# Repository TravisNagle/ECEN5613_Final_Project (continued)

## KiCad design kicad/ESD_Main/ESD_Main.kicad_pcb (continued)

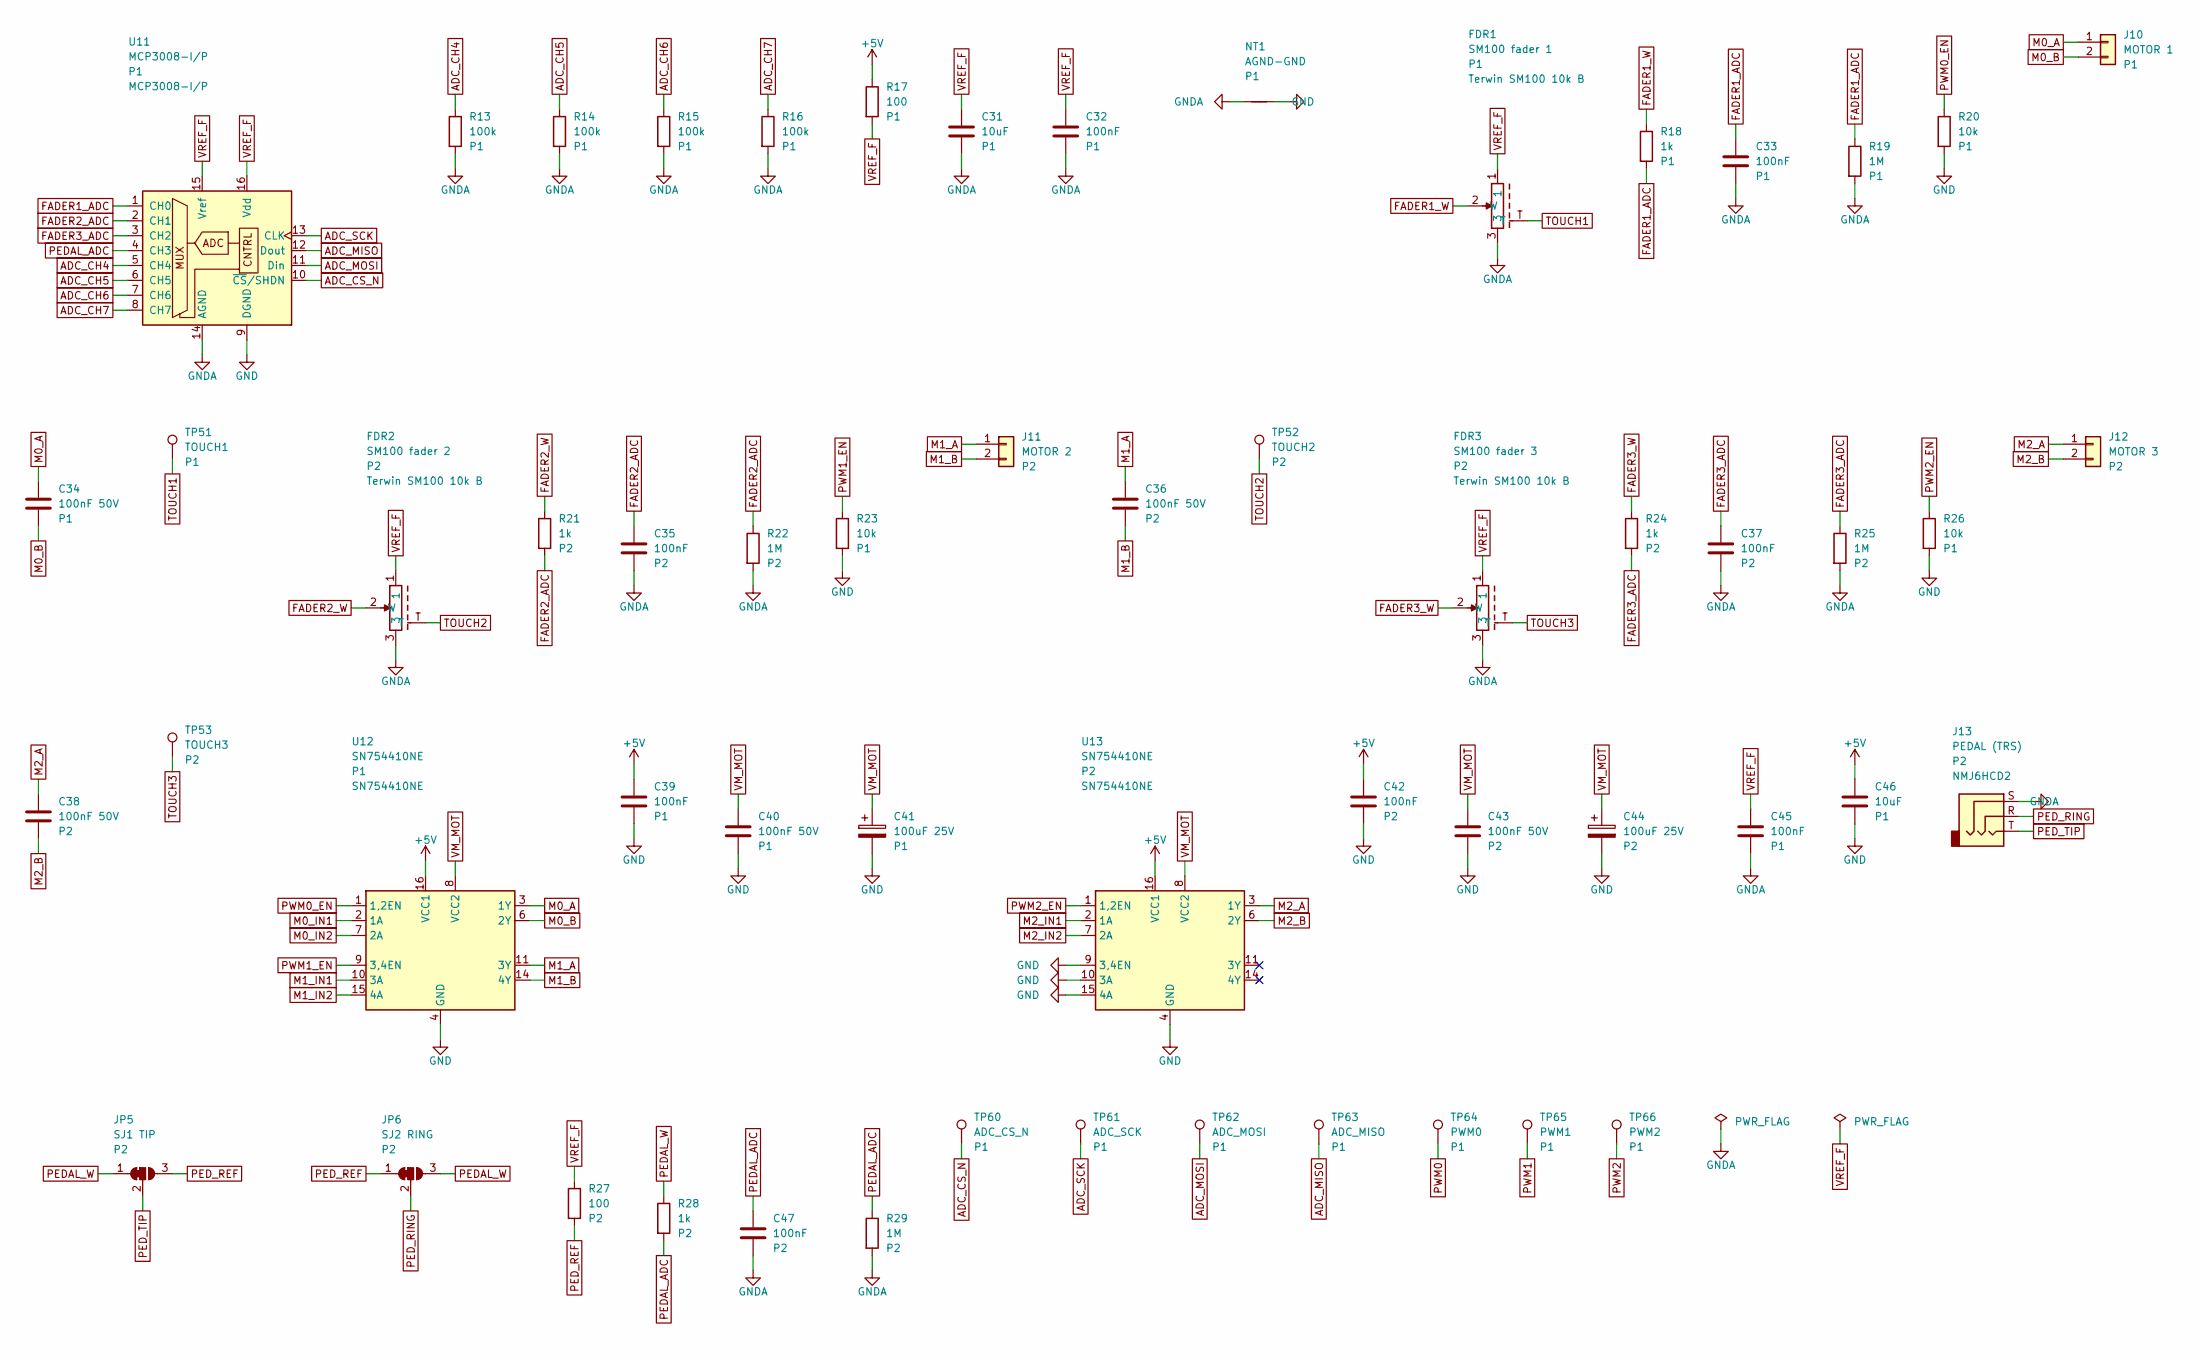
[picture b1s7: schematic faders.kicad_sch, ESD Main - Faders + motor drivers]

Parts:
C31, C46: 10uF; C_0805_2012Metric
C32, C33, C35, C37, C39, C42, C45, C47: 100nF; C_0805_2012Metric
C34, C36, C38, C40, C43: 100nF 50V; C_0805_2012Metric
C41, C44: 100uF 25V; CP_Radial_D6.3mm_P2.50mm
FDR1: SM100 fader 1; Fader_SM100_100mm; MPN Terwin SM100 10k B
FDR2: SM100 fader 2; Fader_SM100_100mm; MPN Terwin SM100 10k B
FDR3: SM100 fader 3; Fader_SM100_100mm; MPN Terwin SM100 10k B
J10: MOTOR 1; PinHeader_1x02_P2.54mm_Vertical
J11: MOTOR 2; PinHeader_1x02_P2.54mm_Vertical
J12: MOTOR 3; PinHeader_1x02_P2.54mm_Vertical
J13: PEDAL (TRS); Jack_6.35mm_Neutrik_NMJ6HCD2_Horizontal; MPN NMJ6HCD2
JP5: SJ1 TIP; SolderJumper-3_P1.3mm_Open_RoundedPad1.0x1.5mm
JP6: SJ2 RING; SolderJumper-3_P1.3mm_Open_RoundedPad1.0x1.5mm
NT1: AGND-GND; NetTie-2_SMD_Pad0.5mm
R13, R14, R15, R16: 100k; R_0805_2012Metric
R17, R27: 100; R_0805_2012Metric
R18, R21, R24, R28: 1k; R_0805_2012Metric
R19, R22, R25, R29: 1M; R_0805_2012Metric
R20, R23, R26: 10k; R_0805_2012Metric
TP51: TOUCH1; TestPoint_THTPad_D1.5mm_Drill0.7mm
TP52: TOUCH2; TestPoint_THTPad_D1.5mm_Drill0.7mm
TP53: TOUCH3; TestPoint_THTPad_D1.5mm_Drill0.7mm
TP60: ADC_CS_N; TestPoint_THTPad_D1.5mm_Drill0.7mm
TP61: ADC_SCK; TestPoint_THTPad_D1.5mm_Drill0.7mm
TP62: ADC_MOSI; TestPoint_THTPad_D1.5mm_Drill0.7mm
TP63: ADC_MISO; TestPoint_THTPad_D1.5mm_Drill0.7mm
TP64: PWM0; TestPoint_THTPad_D1.5mm_Drill0.7mm
TP65: PWM1; TestPoint_THTPad_D1.5mm_Drill0.7mm
TP66: PWM2; TestPoint_THTPad_D1.5mm_Drill0.7mm
U11: MCP3008-I/P; DIP-16_W7.62mm_Socket; MPN MCP3008-I/P
U12, U13: SN754410NE; DIP-16_W7.62mm_Socket; MPN SN754410NE

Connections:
+5V: C39.1, C42.1, C46.1, R17.1, U12.16 (VCC1), U13.16 (VCC1); also elsewhere on the board
ADC_CH4: R13.1, U11.5 (CH4)
ADC_CH5: R14.1, U11.6 (CH5)
ADC_CH6: R15.1, U11.7 (CH6)
ADC_CH7: R16.1, U11.8 (CH7)
ADC_CS_N: TP60.1, U11.10 (~CS/SHDN); also elsewhere on the board
ADC_MISO: TP63.1, U11.12 (Dout); also elsewhere on the board
ADC_MOSI: TP62.1, U11.11 (Din); also elsewhere on the board
ADC_SCK: TP61.1, U11.13 (CLK); also elsewhere on the board
FADER1_ADC: C33.1, R18.2, R19.1, U11.1 (CH0)
FADER1_W: FDR1.2 (W), R18.1
FADER2_ADC: C35.1, R21.2, R22.1, U11.2 (CH1)
FADER2_W: FDR2.2 (W), R21.1
FADER3_ADC: C37.1, R24.2, R25.1, U11.3 (CH2)
FADER3_W: FDR3.2 (W), R24.1
GND: C39.2, C40.2, C41.2, C42.2, C43.2, C44.2, C46.2, NT1.2, R20.2, R23.2, R26.2, U11.9 (DGND), U12.4 (GND), U12.5 (GND), U12.12 (GND), U12.13 (GND), U13.4 (GND), U13.5 (GND), U13.9 (3,4EN), U13.10 (3A), U13.12 (GND), U13.13 (GND), U13.15 (4A); also elsewhere on the board
GNDA: C31.2, C32.2, C33.2, C35.2, C37.2, C45.2, C47.2, FDR1.3, FDR2.3, FDR3.3, J13.S, NT1.1, R13.2, R14.2, R15.2, R16.2, R19.2, R22.2, R25.2, R29.2, U11.14 (AGND)
M0_A: C34.1, J10.1, U12.3 (1Y)
M0_B: C34.2, J10.2, U12.6 (2Y)
M0_IN1: U12.2 (1A); also elsewhere on the board
M0_IN2: U12.7 (2A); also elsewhere on the board
M1_A: C36.1, J11.1, U12.11 (3Y)
M1_B: C36.2, J11.2, U12.14 (4Y)
M1_IN1: U12.10 (3A); also elsewhere on the board
M1_IN2: U12.15 (4A); also elsewhere on the board
M2_A: C38.1, J12.1, U13.3 (1Y)
M2_B: C38.2, J12.2, U13.6 (2Y)
M2_IN1: U13.2 (1A); also elsewhere on the board
M2_IN2: U13.7 (2A); also elsewhere on the board
PEDAL_ADC: C47.1, R28.2, R29.1, U11.4 (CH3)
PEDAL_W: JP5.1 (A), JP6.3 (B), R28.1
PED_REF: JP5.3 (B), JP6.1 (A), R27.2
PED_RING: J13.R, JP6.2 (C)
PED_TIP: J13.T, JP5.2 (C)
PWM0: TP64.1; also elsewhere on the board
PWM0_EN: R20.1, U12.1 (1,2EN); also elsewhere on the board
PWM1: TP65.1; also elsewhere on the board
PWM1_EN: R23.1, U12.9 (3,4EN); also elsewhere on the board
PWM2: TP66.1; also elsewhere on the board
PWM2_EN: R26.1, U13.1 (1,2EN); also elsewhere on the board
TOUCH1: FDR1.T, TP51.1
TOUCH2: FDR2.T, TP52.1
TOUCH3: FDR3.T, TP53.1
VM_MOT: C40.1, C41.1, C43.1, C44.1, U12.8 (VCC2), U13.8 (VCC2); also elsewhere on the board
VREF_F: C31.1, C32.1, C45.1, FDR1.1, FDR2.1, FDR3.1, R17.2, R27.1, U11.15 (Vref), U11.16 (Vdd)

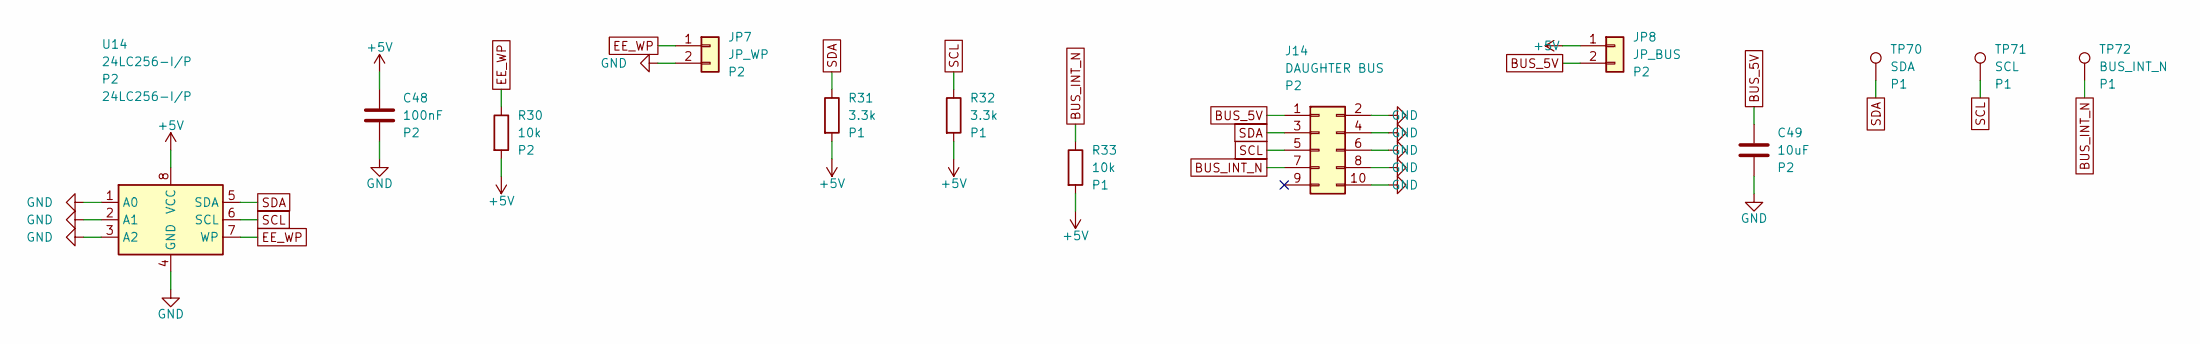
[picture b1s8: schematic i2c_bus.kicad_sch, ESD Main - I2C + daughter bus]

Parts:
C48: 100nF; C_0805_2012Metric
C49: 10uF; C_0805_2012Metric
J14: DAUGHTER BUS; IDC-Header_2x05_P2.54mm_Vertical
JP7: JP_WP; PinHeader_1x02_P2.54mm_Vertical
JP8: JP_BUS; PinHeader_1x02_P2.54mm_Vertical
R30, R33: 10k; R_0805_2012Metric
R31, R32: 3.3k; R_0805_2012Metric
TP70: SDA; TestPoint_THTPad_D1.5mm_Drill0.7mm
TP71: SCL; TestPoint_THTPad_D1.5mm_Drill0.7mm
TP72: BUS_INT_N; TestPoint_THTPad_D1.5mm_Drill0.7mm
U14: 24LC256-I/P; DIP-8_W7.62mm_Socket; MPN 24LC256-I/P

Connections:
+5V: C48.1, JP8.1, R30.2, R31.2, R32.2, R33.2, U14.8 (VCC); also elsewhere on the board
BUS_5V: C49.1, J14.1, JP8.2
BUS_INT_N: J14.7, R33.1, TP72.1; also elsewhere on the board
EE_WP: JP7.1, R30.1, U14.7 (WP)
GND: C48.2, C49.2, J14.2, J14.4, J14.6, J14.8, J14.10, JP7.2, U14.1 (A0), U14.2 (A1), U14.3 (A2), U14.4 (GND); also elsewhere on the board
SCL: J14.5, R32.1, TP71.1, U14.6 (SCL); also elsewhere on the board
SDA: J14.3, R31.1, TP70.1, U14.5 (SDA); also elsewhere on the board

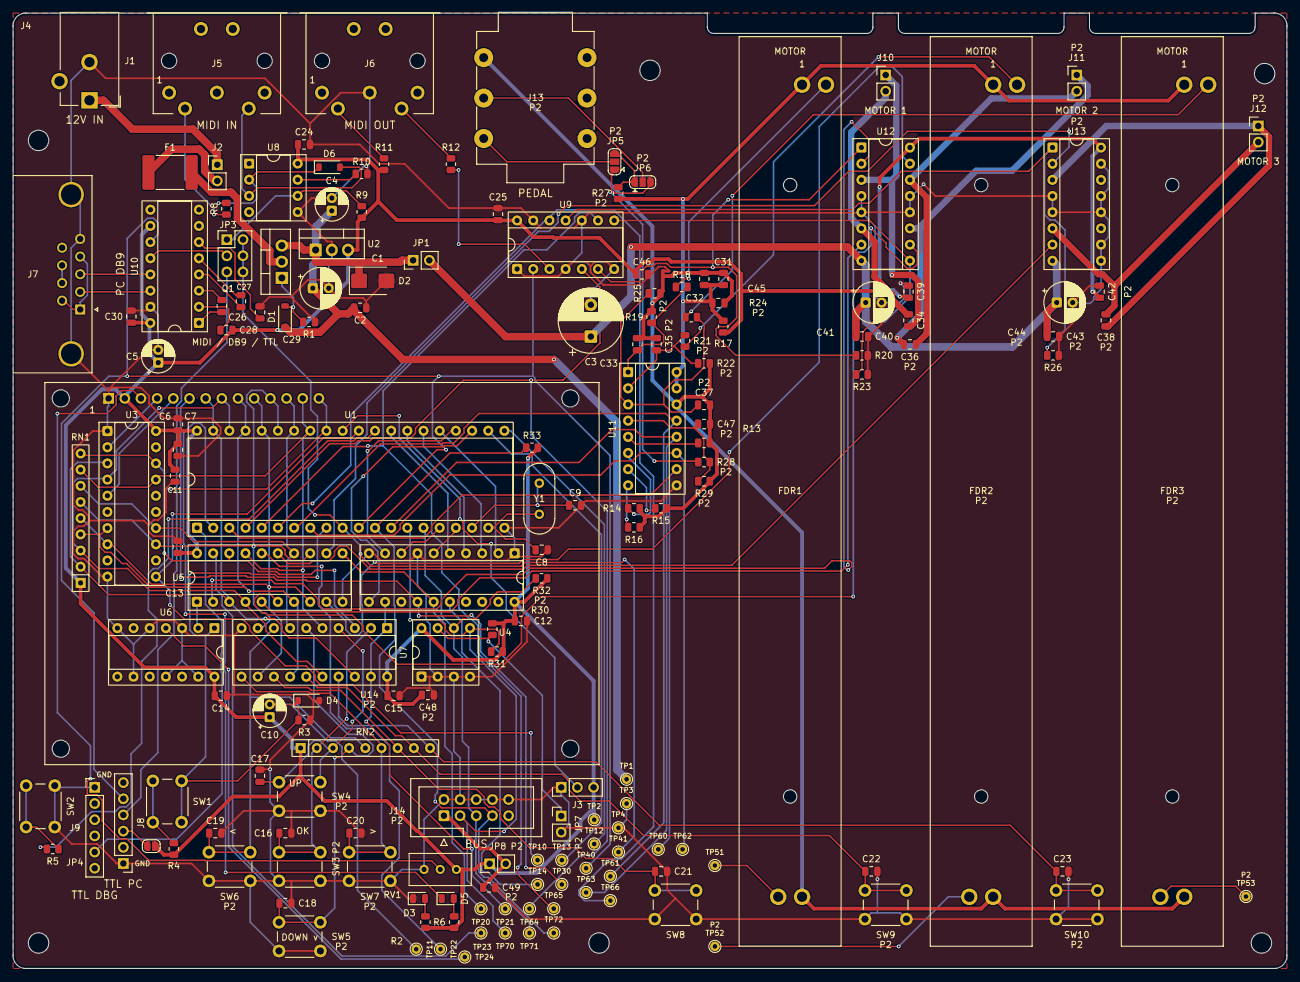
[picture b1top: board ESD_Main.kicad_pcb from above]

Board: 2 copper layers, 200.0 x 150.0 mm, 178 parts (0 on the bottom side), 127 nets.

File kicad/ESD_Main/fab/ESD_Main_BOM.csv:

Ref,Value,Footprint,Phase,Manufacturer PN,Supplier,Supplier URL,Qty,Unit cost
C1,47uF 25V,CP_Radial_D6.3mm_P2.50mm,P1,,,,1,
"C2, C6, C11, C12, C13, C14, C15, C24, C25, C30, C32, C33, C39, C45",100nF,C_0805_2012Metric,P1,,,,14,
C3,470uF 25V,CP_Radial_D10.0mm_P5.00mm,P1,,,,1,
C4,10uF 25V,CP_Radial_D5.0mm_P2.00mm,P1,,,,1,
C5,22uF 10V,CP_Radial_D5.0mm_P2.00mm,P1,,,,1,
"C7, C31, C46",10uF,C_0805_2012Metric,P1,,,,3,
"C8, C9",27pF C0G,C_0805_2012Metric,P1,,,,2,
C10,10uF 16V,CP_Radial_D5.0mm_P2.00mm,P1,,,,1,
"C16, C17, C18, C19, C20, C21, C22, C23",10nF [DNP],C_0805_2012Metric,P1,,,,8,
"C26, C27, C28, C29",1uF 25V,C_0805_2012Metric,P1,,,,4,
"C34, C40",100nF 50V,C_0805_2012Metric,P1,,,,2,
"C35, C37, C42, C47, C48",100nF,C_0805_2012Metric,P2,,,,5,
"C36, C38, C43",100nF 50V,C_0805_2012Metric,P2,,,,3,
C41,100uF 25V,CP_Radial_D6.3mm_P2.50mm,P1,,,,1,
C44,100uF 25V,CP_Radial_D6.3mm_P2.50mm,P2,,,,1,
C49,10uF,C_0805_2012Metric,P2,,,,1,
D1,BZT52C15,D_SOD-123,P1,BZT52C15,,,1,
D2,SMBJ15CA,D_SMB,P1,SMBJ15CA,,,1,
D3,PWR green,LED_0805_2012Metric,P1,,,,1,
"D4, D6",1N4148W,D_SOD-123,P1,,,,2,
D5,STATUS,LED_0805_2012Metric,P1,,,,1,
F1,3A hold,Fuse_2920_7451Metric,P1,2920L300/24MR,,,1,
FDR1,SM100 fader 1,Fader_SM100_100mm,P1,Terwin SM100 10k B,,,1,
FDR2,SM100 fader 2,Fader_SM100_100mm,P2,Terwin SM100 10k B,,,1,
FDR3,SM100 fader 3,Fader_SM100_100mm,P2,Terwin SM100 10k B,,,1,
"H1, H2, H3, H4, H5, H6",M3,MountingHole_3.2mm_M3,P1,,,,6,
J1,12V 3A DC in,BarrelJack_CUI_PJ-102AH_Horizontal,P1,PJ-102AH,,,1,
J2,PWR SW,PinHeader_1x02_P2.54mm_Vertical,P1,,,,1,
J3,EA select,PinHeader_1x03_P2.54mm_Vertical,P1,,,,1,
J4,LCD 16x4 Samsung (Lab 4),LCD_16x4_Samsung_87x60_Header1x14,P1,Samsung SMC1640A (Lab 4 kit),,,1,
J5,MIDI IN,DIN-5_180deg_SameSky_SDS-50J,P1,SDS-50J,,,1,
J6,MIDI OUT,DIN-5_180deg_SameSky_SDS-50J,P1,SDS-50J,,,1,
J7,PC serial (DB9 F),DSUB-9_Socket_Horizontal_P2.77x2.84mm_EdgePinOffset7.70mm_Housed_MountingHolesOffset9.12mm,P1,,,,1,
J8,TTL PC/MIDI (FTDI),PinHeader_1x06_P2.54mm_Vertical,P1,,,,1,
J9,TTL DEBUG (FTDI),PinHeader_1x06_P2.54mm_Vertical,P1,,,,1,
J10,MOTOR 1,PinHeader_1x02_P2.54mm_Vertical,P1,,,,1,
J11,MOTOR 2,PinHeader_1x02_P2.54mm_Vertical,P2,,,,1,
J12,MOTOR 3,PinHeader_1x02_P2.54mm_Vertical,P2,,,,1,
J13,PEDAL (TRS),Jack_6.35mm_Neutrik_NMJ6HCD2_Horizontal,P2,NMJ6HCD2,,,1,
J14,DAUGHTER BUS,IDC-Header_2x05_P2.54mm_Vertical,P2,,,,1,
JP1,JP_VM,PinHeader_1x02_P2.54mm_Vertical,P1,,,,1,
JP3,JP_RX MIDI/DB9/TTL,PinHeader_2x03_P2.54mm_Vertical,P1,,,,1,
JP4,SJ3 TTL VCC,SolderJumper-2_P1.3mm_Open_RoundedPad1.0x1.5mm,P1,,,,1,
JP5,SJ1 TIP,SolderJumper-3_P1.3mm_Open_RoundedPad1.0x1.5mm,P2,,,,1,
JP6,SJ2 RING,SolderJumper-3_P1.3mm_Open_RoundedPad1.0x1.5mm,P2,,,,1,
JP7,JP_WP,PinHeader_1x02_P2.54mm_Vertical,P2,,,,1,
JP8,JP_BUS,PinHeader_1x02_P2.54mm_Vertical,P2,,,,1,
NT1,AGND-GND,NetTie-2_SMD_Pad0.5mm,P1,,,,1,
Q1,IRF4905,TO-220-3_Vertical,P1,IRF4905PBF,,,1,
"R1, R3, R20, R23, R26, R33",10k,R_0805_2012Metric,P1,,,,6,
"R2, R5, R18",1k,R_0805_2012Metric,P1,,,,3,
"R4, R17",100,R_0805_2012Metric,P1,,,,2,
R6,330,R_0805_2012Metric,P1,,,,1,
"R8, R11, R12",220,R_0805_2012Metric,P1,,,,3,
R9,470,R_0805_2012Metric,P1,,,,1,
R10,10k [DNP],R_0805_2012Metric,P1,,,,1,
"R13, R14, R15, R16",100k,R_0805_2012Metric,P1,,,,4,
R19,1M,R_0805_2012Metric,P1,,,,1,
"R21, R24, R28",1k,R_0805_2012Metric,P2,,,,3,
"R22, R25, R29",1M,R_0805_2012Metric,P2,,,,3,
R27,100,R_0805_2012Metric,P2,,,,1,
R30,10k,R_0805_2012Metric,P2,,,,1,
"R31, R32",3.3k,R_0805_2012Metric,P1,,,,2,
"RN1, RN2",10k x8,R_Array_SIP9,P1,,,,2,
RV1,10k contrast,Potentiometer_Bourns_3296W_Vertical,P1,,,,1,
SW1,RESET,SW_PUSH_6mm,P1,,,,1,
SW2,BOOT (PSEN),SW_PUSH_6mm,P1,,,,1,
SW3,CENTER,SW_PUSH_6mm,P2,,,,1,
SW4,UP,SW_PUSH_6mm,P2,,,,1,
SW5,DOWN,SW_PUSH_6mm,P2,,,,1,
SW6,LEFT,SW_PUSH_6mm,P2,,,,1,
SW7,RIGHT,SW_PUSH_6mm,P2,,,,1,
SW8,F1,SW_PUSH_6mm,P1,,,,1,
SW9,F2,SW_PUSH_6mm,P2,,,,1,
SW10,F3,SW_PUSH_6mm,P2,,,,1,
TP1,VM,TestPoint_THTPad_D1.5mm_Drill0.7mm,P1,,,,1,
TP2,+5V,TestPoint_THTPad_D1.5mm_Drill0.7mm,P1,,,,1,
"TP3, TP4",GND,TestPoint_THTPad_D1.5mm_Drill0.7mm,P1,,,,2,
TP10,ALE,TestPoint_THTPad_D1.5mm_Drill0.7mm,P1,,,,1,
TP11,RST,TestPoint_THTPad_D1.5mm_Drill0.7mm,P1,,,,1,
TP12,A8,TestPoint_THTPad_D1.5mm_Drill0.7mm,P1,,,,1,
TP13,A9,TestPoint_THTPad_D1.5mm_Drill0.7mm,P1,,,,1,
TP14,VDP_WR_N,TestPoint_THTPad_D1.5mm_Drill0.7mm,P1,,,,1,
TP20,MOTDIR_CLK,TestPoint_THTPad_D1.5mm_Drill0.7mm,P1,,,,1,
TP21,BTN_OE_N,TestPoint_THTPad_D1.5mm_Drill0.7mm,P1,,,,1,
TP22,MD_Q6,TestPoint_THTPad_D1.5mm_Drill0.7mm,P1,,,,1,
TP23,MD_Q7,TestPoint_THTPad_D1.5mm_Drill0.7mm,P1,,,,1,
TP24,INV_SPARE,TestPoint_THTPad_D1.5mm_Drill0.7mm,P1,,,,1,
TP30,LCD_E,TestPoint_THTPad_D1.5mm_Drill0.7mm,P1,,,,1,
TP40,MIDI_TX,TestPoint_THTPad_D1.5mm_Drill0.7mm,P1,,,,1,
TP41,MIDI_RX,TestPoint_THTPad_D1.5mm_Drill0.7mm,P1,,,,1,
TP51,TOUCH1,TestPoint_THTPad_D1.5mm_Drill0.7mm,P1,,,,1,
TP52,TOUCH2,TestPoint_THTPad_D1.5mm_Drill0.7mm,P2,,,,1,
TP53,TOUCH3,TestPoint_THTPad_D1.5mm_Drill0.7mm,P2,,,,1,
TP60,ADC_CS_N,TestPoint_THTPad_D1.5mm_Drill0.7mm,P1,,,,1,
TP61,ADC_SCK,TestPoint_THTPad_D1.5mm_Drill0.7mm,P1,,,,1,
TP62,ADC_MOSI,TestPoint_THTPad_D1.5mm_Drill0.7mm,P1,,,,1,
TP63,ADC_MISO,TestPoint_THTPad_D1.5mm_Drill0.7mm,P1,,,,1,
TP64,PWM0,TestPoint_THTPad_D1.5mm_Drill0.7mm,P1,,,,1,
TP65,PWM1,TestPoint_THTPad_D1.5mm_Drill0.7mm,P1,,,,1,
TP66,PWM2,TestPoint_THTPad_D1.5mm_Drill0.7mm,P1,,,,1,
TP70,SDA,TestPoint_THTPad_D1.5mm_Drill0.7mm,P1,,,,1,
TP71,SCL,TestPoint_THTPad_D1.5mm_Drill0.7mm,P1,,,,1,
TP72,BUS_INT_N,TestPoint_THTPad_D1.5mm_Drill0.7mm,P1,,,,1,
U1,AT89C51RC2,DIP-40_W15.24mm_Socket,P1,AT89C51RC2-3CSUM,,,1,
U2,R-78E5.0-1.0,TO-220-3_Vertical,P1,R-78E5.0-1.0,,,1,
U3,SN74LS373N,DIP-20_W7.62mm_Socket,P1,SN74LS373N,,,1,
U4,ATF16V8B-15PU,DIP-20_W7.62mm_Socket,P1,ATF16V8B-15PU,,,1,
U5,74HCT273,DIP-20_W7.62mm_Socket,P1,SN74HCT273N,,,1,
U6,74HC14,DIP-14_W7.62mm_Socket,P1,SN74HC14N,,,1,
U7,74HC244,DIP-20_W7.62mm_Socket,P1,SN74HC244N,,,1,
U8,6N138,DIP-8_W7.62mm_Socket,P1,6N138M (Lite-On),,,1,
U9,74HCT125,DIP-14_W7.62mm_Socket,P1,SN74HCT125N,,,1,
U10,MAX232,DIP-16_W7.62mm_Socket,P1,MAX232N,,,1,
U11,MCP3008-I/P,DIP-16_W7.62mm_Socket,P1,MCP3008-I/P,,,1,
U12,SN754410NE,DIP-16_W7.62mm_Socket,P1,SN754410NE,,,1,
U13,SN754410NE,DIP-16_W7.62mm_Socket,P2,SN754410NE,,,1,
U14,24LC256-I/P,DIP-8_W7.62mm_Socket,P2,24LC256-I/P,,,1,
Y1,11.0592MHz,Crystal_HC49-U_Vertical,P1,,,,1,

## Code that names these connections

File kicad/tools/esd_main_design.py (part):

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
# ---------------------------------------------------------------- power
part("J1", "Connector:Barrel_Jack_Switch", "12V 3A DC in", "Connector_BarrelJack:BarrelJack_CUI_PJ-102AH_Horizontal",
     "power", {"1": "VIN_RAW", "2": "GND"}, mpn="PJ-102AH", note="2.1 mm, centre positive; pin 3 (switch) NC")
part("J2", "Connector_Generic:Conn_01x02", "PWR SW", FP_H2, "power", {"1": "VIN_RAW", "2": "VIN_SW"},
     note="SW1: off-board panel toggle switch rated >= 3 A on this header")
part("F1", "Device:Polyfuse", "3A hold", "Fuse:Fuse_2920_7451Metric", "power", {"1": "VIN_SW", "2": "VIN_F"},
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decouple("C6", "+5V", "mcu_bus")
C("C7", "10uF", "+5V", "GND", "mcu_bus", note="bulk near U1")
part("Y1", "Device:Crystal", "11.0592MHz", "Crystal:Crystal_HC49-U_Vertical", "mcu_bus",
     {"1": "XTAL1", "2": "XTAL2"}, note="fit in 2 machined-pin receptacles (socketed; 16 MHz option)")
C("C8", "27pF C0G", "XTAL1", "GND", "mcu_bus")
C("C9", "27pF C0G", "XTAL2", "GND", "mcu_bus")
# class-board reset: cap to VCC, 10k to GND, button through 100R, negative clamp diode
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
# ---------------------------------------------------------------- MIDI + serial
part("J5", "Connector:DIN-5_180degree", "MIDI IN", "ESD:DIN-5_180deg_SameSky_SDS-50J", "midi_serial",
     {"4": "MIDI_IN_4", "5": "MIDI_IN_5"}, mpn="SDS-50J", note="J8 in spec; pin 2 and shield NC on IN")
R("R8", "220", "MIDI_IN_4", "OPTO_A", "midi_serial")
part("D6", "Diode:1N4148W", "1N4148W", FP_D, "midi_serial", {"1": "OPTO_A", "2": "MIDI_IN_5"},
     note="reverse protection across opto LED")
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part("U12", "Driver_Motor:SN754410NE", "SN754410NE", FP_DIP[16], "faders",
     {"1": "PWM0_EN", "2": "M0_IN1", "3": "M0_A", "4": "GND", "5": "GND", "6": "M0_B", "7": "M0_IN2",
      "8": "VM_MOT", "9": "PWM1_EN", "10": "M1_IN1", "11": "M1_A", "12": "GND", "13": "GND", "14": "M1_B",
      "15": "M1_IN2", "16": "+5V"}, mpn="SN754410NE", note="motors 0 and 1; GND pins 4,5,12,13 to copper pour")
decouple("C39", "+5V", "faders")
C("C40", "100nF 50V", "VM_MOT", "GND", "faders")
CP("C41", "100uF 25V", "VM_MOT", "GND", "faders", "Capacitor_THT:CP_Radial_D6.3mm_P2.50mm")
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
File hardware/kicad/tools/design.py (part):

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
CABLES = [
    "Inter-board connections:",
    "J20 (class) <-> J30 (D-pad)   12-pin ribbon, about 9 in: AD0-AD7, LCD_RS, LCD_RW, LCD_E, GND",
    "J21 (class) <-> J31 (D-pad)   10-pin ribbon, about 8 in: +5V, GND x2, BTN_OE_N, TOUCH2, ADC SPI, 1 spare",
    "J22 (class) --> FDR1, FDR2 motors   4 wires (two twisted pairs)",
    "J32 (D-pad) <-> J40 (fader strip)   6 wires: +5V, GND, BTN_F1, BTN_F2, TOUCH1, TOUCH2",
    "J33 (D-pad) --> LCD1   14 wires;  J34 (D-pad) --> FDR1/FDR2 pots   4 wires;  J35 (D-pad) --> J13 pedal jack   3 wires",
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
